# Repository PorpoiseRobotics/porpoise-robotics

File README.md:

# Porpoise Robotics

> Code, hardware notes, and documentation for the Porpoise Robotics vehicle and camera projects.

Porpoise Robotics is an educational robotics organization based in Rancho Bernardo, California,
built around the idea of teaching **STEM and AI through unmanned vehicles**. In the
organization's own words, its purpose is "to revolutionize STEM education through innovative
robotic platforms that combine cutting-edge technology with hands-on learning experiences,"
serving students and educators. Learn more at
[porpoiserobotics.org](https://www.porpoiserobotics.org/).

This repository is where the engineering work lives: source code, design documents, and build
notes for four projects — plus one folder holding code they share.

---

## New to git? Start here.

**If you have never used git or GitHub before, do not start by reading this file.**
Go to the guides in [`docs/`](docs/) and work through them in order. They assume zero prior
experience — no terminal, no GitHub account, nothing.

| Read this | When |
|---|---|
| [Installing git and setting it up](docs/01-install-git.md) | First, once per computer |
| [The everyday workflow](docs/02-everyday-workflow.md) | Second, then keep it open while you work |
| [Plain-English glossary](docs/03-glossary.md) | Any time a word doesn't make sense |
| [When things go wrong](docs/04-when-things-go-wrong.md) | The moment anything looks scary |
| [Why empty folders have a `.gitkeep` file](docs/05-gitkeep-and-empty-folders.md) | When you notice those odd empty files |

Also read [CONTRIBUTING.md](CONTRIBUTING.md) before your first change. It is short on purpose.

---

## What is in this repository

Four projects, each in its own top-level folder:

### [`homeland-security-camera/`](homeland-security-camera/README.md)
A security camera system intended for **deployment at a school**. Because it involves a camera
system on a campus, this project has stricter rules about what may be written down here — see
its README before contributing. It now has its first code: a camera node and a perimeter sensor
node that talk to each other over radio, with no router or server between them.

### [`ground-vehicle/`](ground-vehicle/README.md)
A ground-based unmanned vehicle platform — a rover that drives on land. This is where the
Pathfinder operating programs live. Note that the Pathfinder rover is a different vehicle from
the "Pathfinder ROV" mentioned below, despite the shared name.

### [`submersible-vehicle/`](submersible-vehicle/README.md)
An underwater vehicle platform. Porpoise Robotics publicly lists two ROV platforms, Explorer ROV
and Pathfinder ROV; the team should confirm which of these this folder covers and record that in
the project README.

### [`find-the-target/`](find-the-target/README.md)
A STEM mission activity: up to nine stations, each a laptop plus a vehicle with a camera, GPS
and sensors, share one field. Version 5 runs on the PorpoiseNet radio network, so stations can
chat and drop marks on each other's maps. Includes the sensor circuit board (KiCad) and the
slides and setup guide students follow.

### [`shared/`](shared/README.md)
Not a project — code that more than one project uses, so a fix made once is a fix everywhere.
Today that is [**PorpoiseNet**](shared/PorpoiseNet/README.md), the two-way ESP-NOW radio layer
that both the Find the Target mesh variant and the security camera system run on.

Every *project* folder has the same starter layout:

```
project-name/
├── README.md      what this project is and how to work on it
├── src/           source code
├── docs/          design notes, diagrams, decisions
└── hardware/      wiring notes, bill of materials, mechanical files
```

**Most of those folders are still empty.** That is expected — most of the code has not been
written yet. An empty one contains a file called `.gitkeep`, which exists purely so that git will
keep the folder. [Here is why that is necessary.](docs/05-gitkeep-and-empty-folders.md) Delete the
`.gitkeep` once a folder has real files in it.

Where a project has code that has been replaced but is worth keeping, it lives in a `legacy/`
folder inside `src/`, with a README saying what replaced it and why.

---

## This repository is public

Anyone on the internet can read everything in here, including its full history. That is a
deliberate decision by the organization. It means one rule matters more than any other:

**Do not commit anything sensitive.** No passwords, no API keys, no camera credentials, no
network or IP addresses, no school floor plans or camera placement maps, no student information.
Details and the safe way to handle configuration are in
[CONTRIBUTING.md](CONTRIBUTING.md#rule-4-never-commit-secrets).

---

## Status

`ground-vehicle/` holds the team's existing Pathfinder and Find the Target code, moved in from a
OneDrive export, now with a two-way PorpoiseNet mesh option alongside the original telemetry link.
`homeland-security-camera/` has its radio layer and nothing above it — and its privacy questions
are still unanswered, which blocks any actual deployment. `submersible-vehicle/` is still
structure and documentation only. Sections marked **TBD** are waiting on the team.

## License

Not yet chosen — see [LICENSE](LICENSE). The organization needs to decide this before the
repository is published publicly.

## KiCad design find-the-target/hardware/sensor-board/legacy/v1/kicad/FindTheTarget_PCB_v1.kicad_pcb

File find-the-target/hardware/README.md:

# Find the Target hardware

The circuit boards for Find the Target, drawn in [KiCad](https://www.kicad.org/) (free).

## Sensor board ("Find The Target Sender")

This is the board on the vehicle that carries the sensor ESP32. It runs
`VehicleSensors_v5` (or the older `ESPNow_Sender_v4`). A 38-pin ESP32 plugs into its sockets,
and the board connects it to:

- the FK-A1 GPS and compass (JST-SH cable, J4);
- the HC-SR04 range finder (the board divides the 5 V echo down to 3.3 V);
- the BMP280 temperature and pressure sensor on the same I2C pins as the compass;
- the NeoPixel LED ring, through a 74AHCT125 level shifter;
- 5 V power through a polyfuse, reverse-polarity MOSFET and surge diode.

The **latest revision is Rev 0.5**: 2 layers, 85 × 85 mm, all parts on the top side.

| Folder | What is in it |
|---|---|
| [`sensor-board/rev-0.5/kicad/`](sensor-board/rev-0.5/kicad/) | The KiCad project. Open `FindTheTarget_PCB_v1.kicad_pro`. (The file name still says v1; the title block says Rev 0.5.) The project's own symbol and footprint libraries sit next to it. |
| [`sensor-board/rev-0.5/order-files/`](sensor-board/rev-0.5/order-files/) | Everything a board house needs: Gerbers and drill files (zip), the parts list with manufacturer part numbers, the pick-and-place file, and **assembly notes to paste into the order**. |
| [`sensor-board/rev-0.5/review/`](sensor-board/rev-0.5/review/) | PDFs and pictures to look at without KiCad: schematic, board layout, 3D renders, and the clean design-rule (DRC) and electrical-rule (ERC) reports. |
| [`sensor-board/legacy/v1/`](sensor-board/legacy/v1/) | The first board (August 2026). Kept for reference; do not order it. |

### To order more boards

1. Upload `order-files/FindTheTarget_Rev0.5_Gerbers.zip` to the board house.
2. Choose 2 layers, 1.6 mm, FR-4. The other settings are in `ASSEMBLY_NOTES.txt`.
3. For assembled boards, also upload the BOM and Centroid files, and paste the
   "Notes for the assembler" section of `ASSEMBLY_NOTES.txt` into the order comments.
   **Solder jumper JP1 must be bridged to "B"** (level-shifted LED data).
4. Buy the parts listed under "Not on the board" in the same file: the ESP32, the FK-A1
   with its cable, JST-XH plugs, the LED ring, and M3 screws and standoffs.

The Rev 0.5 Gerbers were checked on 2026-11-22: exporting them again from the KiCad project
in this folder gives identical copper, mask, paste, silkscreen and outline layers. The last
change (D3 swapped to the MBR230LSFT1G diode on 2026-11-06) kept the same footprint, so it
only changed the parts list.

### If you change the board

1. Make the change in KiCad, then run **Inspect → Design Rules Checker** and fix what it finds.
2. Bump the revision in **File → Page Settings** (the title block) and on the silkscreen.
3. Make a new `rev-X.Y/` folder next to `rev-0.5/` with fresh Gerbers, BOM, centroid file,
   schematic PDF and DRC report, and move the old revision into `legacy/`.

KiCad also writes backup folders, a `.kicad_prl` file (your window layout) and lock files.
Git ignores those on purpose: only the project, schematic, board and library files belong here.

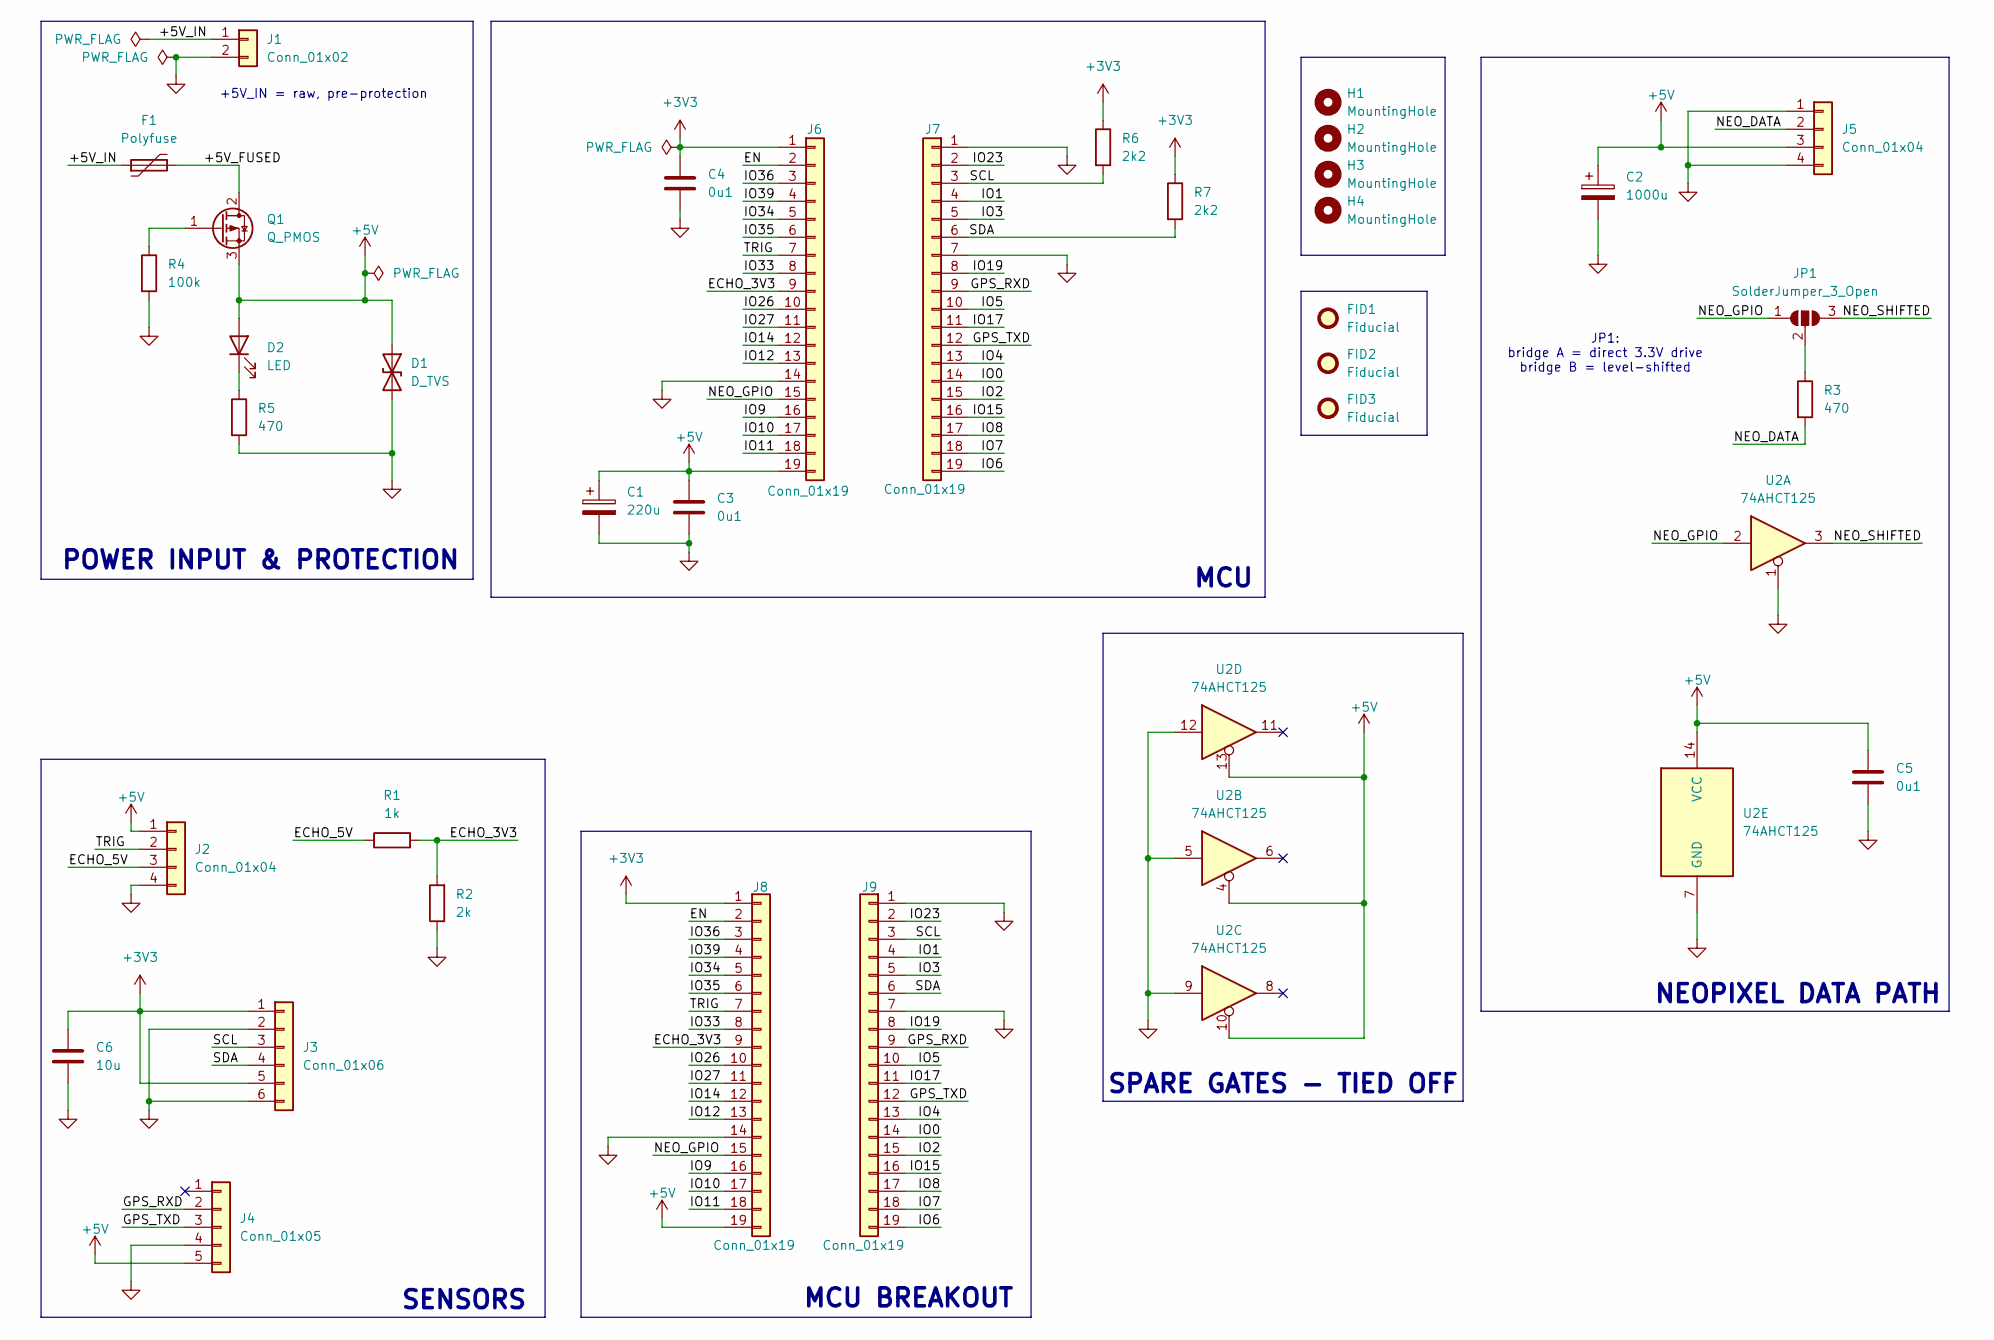
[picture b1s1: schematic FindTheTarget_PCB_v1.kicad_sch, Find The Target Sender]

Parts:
C1: 220u; CP_Elec_8x10.5; MPN EEV227M025A9MAA
C2: 1000u; CP_Elec_10x10.5; MPN EDT108M010S9PAA
C3, C4, C5: 0u1; C_0805_2012Metric; MPN CC0805KRX7R7BB104
C6: 10u; C_0805_2012Metric; MPN C0805C106K4PAC7210
D1: D_TVS; D_SMB; MPN SMBJ5.0CA
D2: LED; LED_0805_2012Metric; MPN 150080GS75000
F1: Polyfuse; Fuse_1812_4532Metric; MPN MF-MSMF250/16X-2
FID1, FID2, FID3: Fiducial; Fiducial_1mm_Mask3mm
H1, H2, H3, H4: MountingHole; MountingHole_3.2mm_M3
J1: Conn_01x02; JST_XH_B2B-XH-A_1x02_P2.50mm_Vertical; MPN B2B-XH-A
J2, J5: Conn_01x04; JST_XH_B4B-XH-A_1x04_P2.50mm_Vertical; MPN B4B-XH-A
J3: Conn_01x06; PinSocket_1x06_P2.54mm_Vertical; MPN 61300611821
J4: Conn_01x05; PinSocket_1x05_P2.54mm_Vertical; MPN 61300511821
J6, J7, J8, J9: Conn_01x19; PinSocket_1x19_P2.54mm_Vertical; MPN PPTC191LFBN-RC
JP1: SolderJumper_3_Open; SolderJumper-3_P1.3mm_Open_RoundedPad1.0x1.5mm
Q1: Q_PMOS; TO-252-2; MPN IPD90P04P4L04ATMA2
R1: 1k; R_0805_2012Metric; MPN CRCW08051K00FKEA
R2: 2k; R_0805_2012Metric; MPN RC0805FR-072KL
R3, R5: 470; R_0805_2012Metric; MPN RC0805FR-07470RL
R4: 100k; R_0805_2012Metric; MPN RC0805FR-07100KL
R6, R7: 2k2; R_0805_2012Metric; MPN RC0805FR-072K2L
U2: 74AHCT125; SOIC-14_3.9x8.7mm_P1.27mm; MPN 74AHCT125S14-13

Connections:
+3V3: C4.1, C6.1, J3.1, J3.5, J6.1, J8.1, R6.1, R7.1
+5V: C1.1, C2.1, C3.1, C5.1, D1.1 (A1), D2.2 (A), J2.1, J4.5, J5.3, J6.19, J8.19, Q1.3 (S), U2.4, U2.10, U2.13, U2.14 (VCC)
/+5V_FUSED: F1.2, Q1.2 (D)
/+5V_IN: F1.1, J1.1
/ECHO_3V3: J6.9, J8.9, R1.2, R2.2
/ECHO_5V: J2.3, R1.1
/EN: J6.2, J8.2
/GPS_RXD: J4.2, J7.9, J9.9
/GPS_TXD: J4.3, J7.12, J9.12
/IO0: J7.14, J9.14
/IO1: J7.4, J9.4
/IO2: J7.15, J9.15
/IO3: J7.5, J9.5
/IO4: J7.13, J9.13
/IO5: J7.10, J9.10
/IO6: J7.19, J9.19
/IO7: J7.18, J9.18
/IO8: J7.17, J9.17
/IO9: J6.16, J8.16
/IO10: J6.17, J8.17
/IO11: J6.18, J8.18
/IO12: J6.13, J8.13
/IO14: J6.12, J8.12
/IO15: J7.16, J9.16
/IO17: J7.11, J9.11
/IO19: J7.8, J9.8
/IO23: J7.2, J9.2
/IO26: J6.10, J8.10
/IO27: J6.11, J8.11
/IO33: J6.8, J8.8
/IO34: J6.5, J8.5
/IO35: J6.6, J8.6
/IO36: J6.3, J8.3
/IO39: J6.4, J8.4
/NEO_DATA: J5.2, R3.2
/NEO_GPIO: J6.15, J8.15, JP1.1 (A), U2.2
/NEO_SHIFTED: JP1.3 (B), U2.3
/SCL: J3.3, J7.3, J9.3, R6.2
/SDA: J3.4, J7.6, J9.6, R7.2
/TRIG: J2.2, J6.7, J8.7
GND: C1.2, C2.2, C3.2, C4.2, C5.2, C6.2, D1.2 (A2), J1.2, J2.4, J3.2, J3.6, J4.4, J5.1, J5.4, J6.14, J7.1, J7.7, J8.14, J9.1, J9.7, R2.1, R4.2, R5.2, U2.1, U2.5, U2.7 (GND), U2.9, U2.12
unnamed: D2.1 (K), R5.1
unnamed: JP1.2 (C), R3.1
unnamed: Q1.1 (G), R4.1

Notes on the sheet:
POWER INPUT & PROTECTION
NEOPIXEL DATA PATH
JP1: bridge A = direct 3.3V drive bridge B = level-shifted
SPARE GATES - TIED OFF
MCU BREAKOUT
MCU
SENSORS
+5V_IN = raw, pre-protection

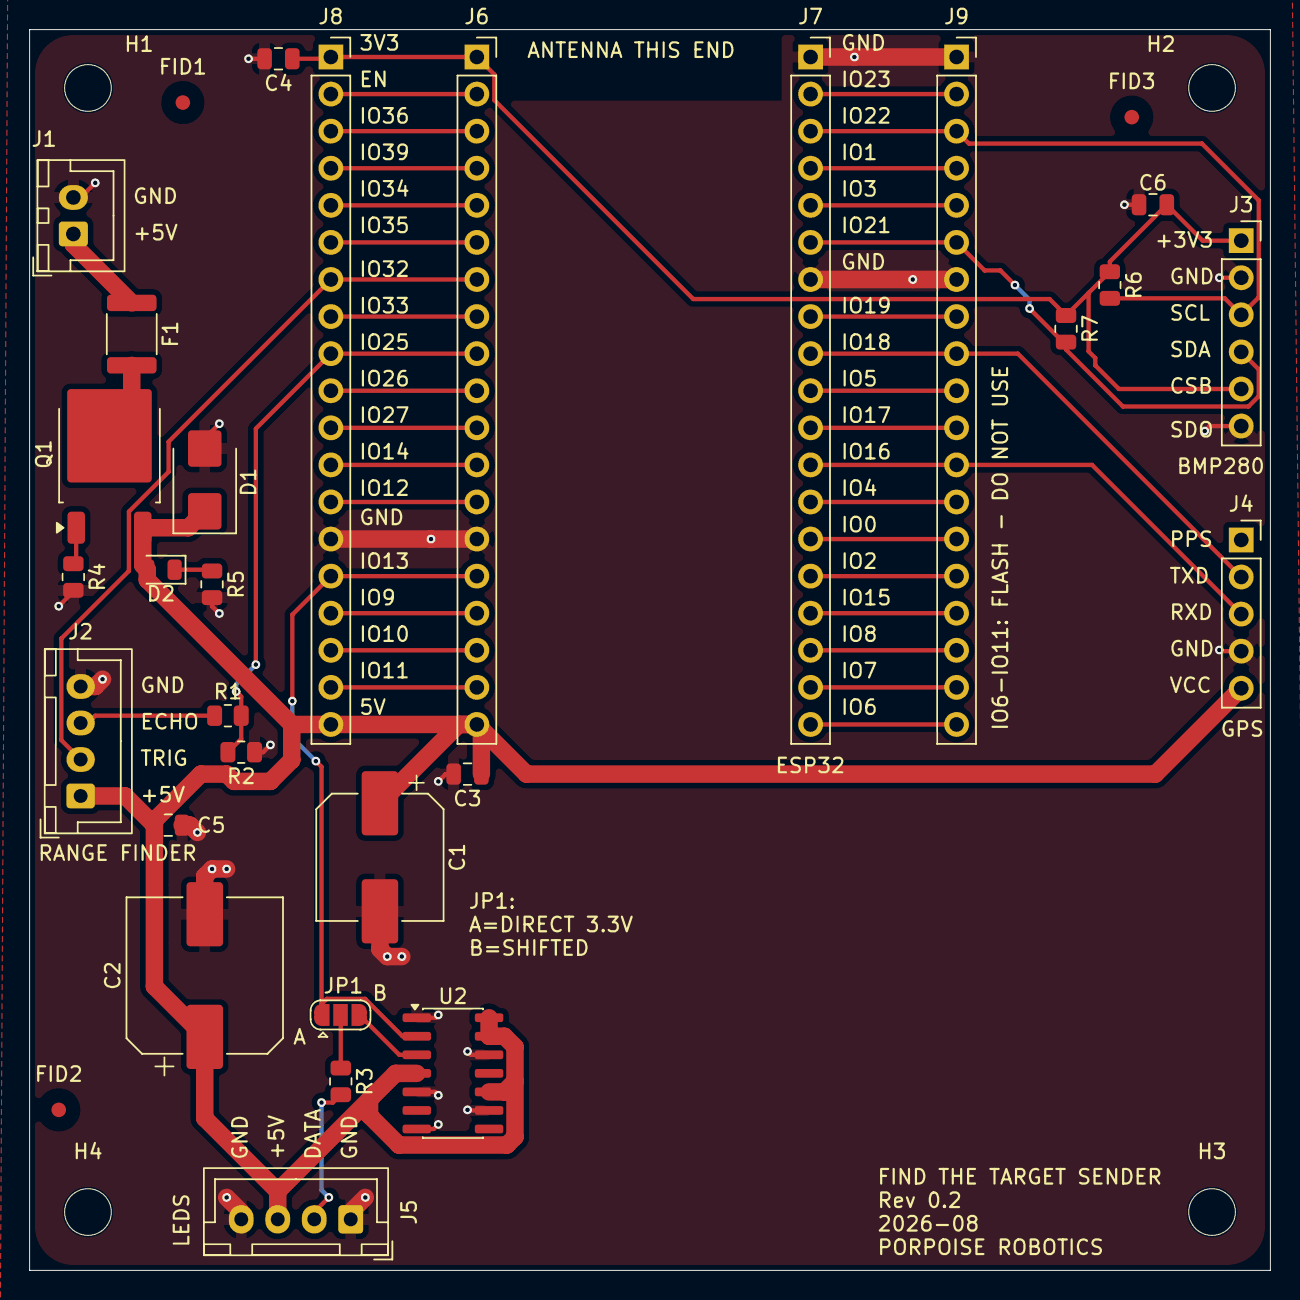
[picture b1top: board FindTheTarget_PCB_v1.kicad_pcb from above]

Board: 2 copper layers, 85.0 x 85.0 mm, 35 parts (0 on the bottom side), 44 nets.

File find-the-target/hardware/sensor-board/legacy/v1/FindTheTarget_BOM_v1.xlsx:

Reference | Qty | Value | DNP | Exclude from BOM | Exclude from Board | Footprint | Datasheet | MPN | Manufacturer
C1 | 1 | 220u |  |  |  | Capacitor_SMD:CP_Elec_8x10.5 |  | EEV227M025A9MAA | KEMET
C2 | 1 | 1000u |  |  |  | Capacitor_SMD:CP_Elec_10x10.5 |  | EDT108M010S9PAA | KEMET
C3,C4,C5 | 3 | 0u1 |  |  |  | Capacitor_SMD:C_0805_2012Metric |  | CC0805KRX7R7BB104 | YAGEO
C6 | 1 | 10u |  |  |  | Capacitor_SMD:C_0805_2012Metric |  | C0805C106K4PAC7210 | KEMET
D1 | 1 | D_TVS |  |  |  | Diode_SMD:D_SMB |  | SMBJ5.0CA | Littelfuse Inc.
D2 | 1 | LED |  |  |  | LED_SMD:LED_0805_2012Metric |  | 150080GS75000 | Würth Elektronik
F1 | 1 | Polyfuse |  |  |  | Fuse:Fuse_1812_4532Metric |  | MF-MSMF250/16X-2 | Bourns Inc.
J1 | 1 | Conn_01x02 |  |  |  | Connector_JST:JST_XH_B2B-XH-A_1x02_P2.50mm_Vertical |  | B2B-XH-A | JST Sales America Inc.
J2,J5 | 2 | Conn_01x04 |  |  |  | Connector_JST:JST_XH_B4B-XH-A_1x04_P2.50mm_Vertical |  | B4B-XH-A | JST Sales America Inc.
J3 | 1 | Conn_01x06 |  |  |  | Connector_PinSocket_2.54mm:PinSocket_1x06_P2.54mm_Vertical |  | 61300611821 | Würth Elektronik
J4 | 1 | Conn_01x05 |  |  |  | Connector_PinSocket_2.54mm:PinSocket_1x05_P2.54mm_Vertical |  | 61300511821 | Würth Elektronik
J6,J7,J8,J9 | 4 | Conn_01x19 |  |  |  | Connector_PinSocket_2.54mm:PinSocket_1x19_P2.54mm_Vertical |  | PPTC191LFBN-RC | Sullins Connector Solutions
Q1 | 1 | Q_PMOS |  |  |  | Package_TO_SOT_SMD:TO-252-2 |  | IPD90P04P4L04ATMA2 | Infineon Technologies
R1 | 1 | 1k |  |  |  | Resistor_SMD:R_0805_2012Metric |  | CRCW08051K00FKEA | Vishay Dale
R2 | 1 | 2k |  |  |  | Resistor_SMD:R_0805_2012Metric |  | RC0805FR-072KL | YAGEO
R3,R5 | 2 | 470 |  |  |  | Resistor_SMD:R_0805_2012Metric |  | RC0805FR-07470RL | YAGEO
R4 | 1 | 100k |  |  |  | Resistor_SMD:R_0805_2012Metric |  | RC0805FR-07100KL | YAGEO
R6,R7 | 2 | 2k2 |  |  |  | Resistor_SMD:R_0805_2012Metric |  | RC0805FR-072K2L | YAGEO
U2 | 1 | 74AHCT125 |  |  |  | Package_SO:SOIC-14_3.9x8.7mm_P1.27mm |  | 74AHCT125S14-13 | Diodes Incorporated
